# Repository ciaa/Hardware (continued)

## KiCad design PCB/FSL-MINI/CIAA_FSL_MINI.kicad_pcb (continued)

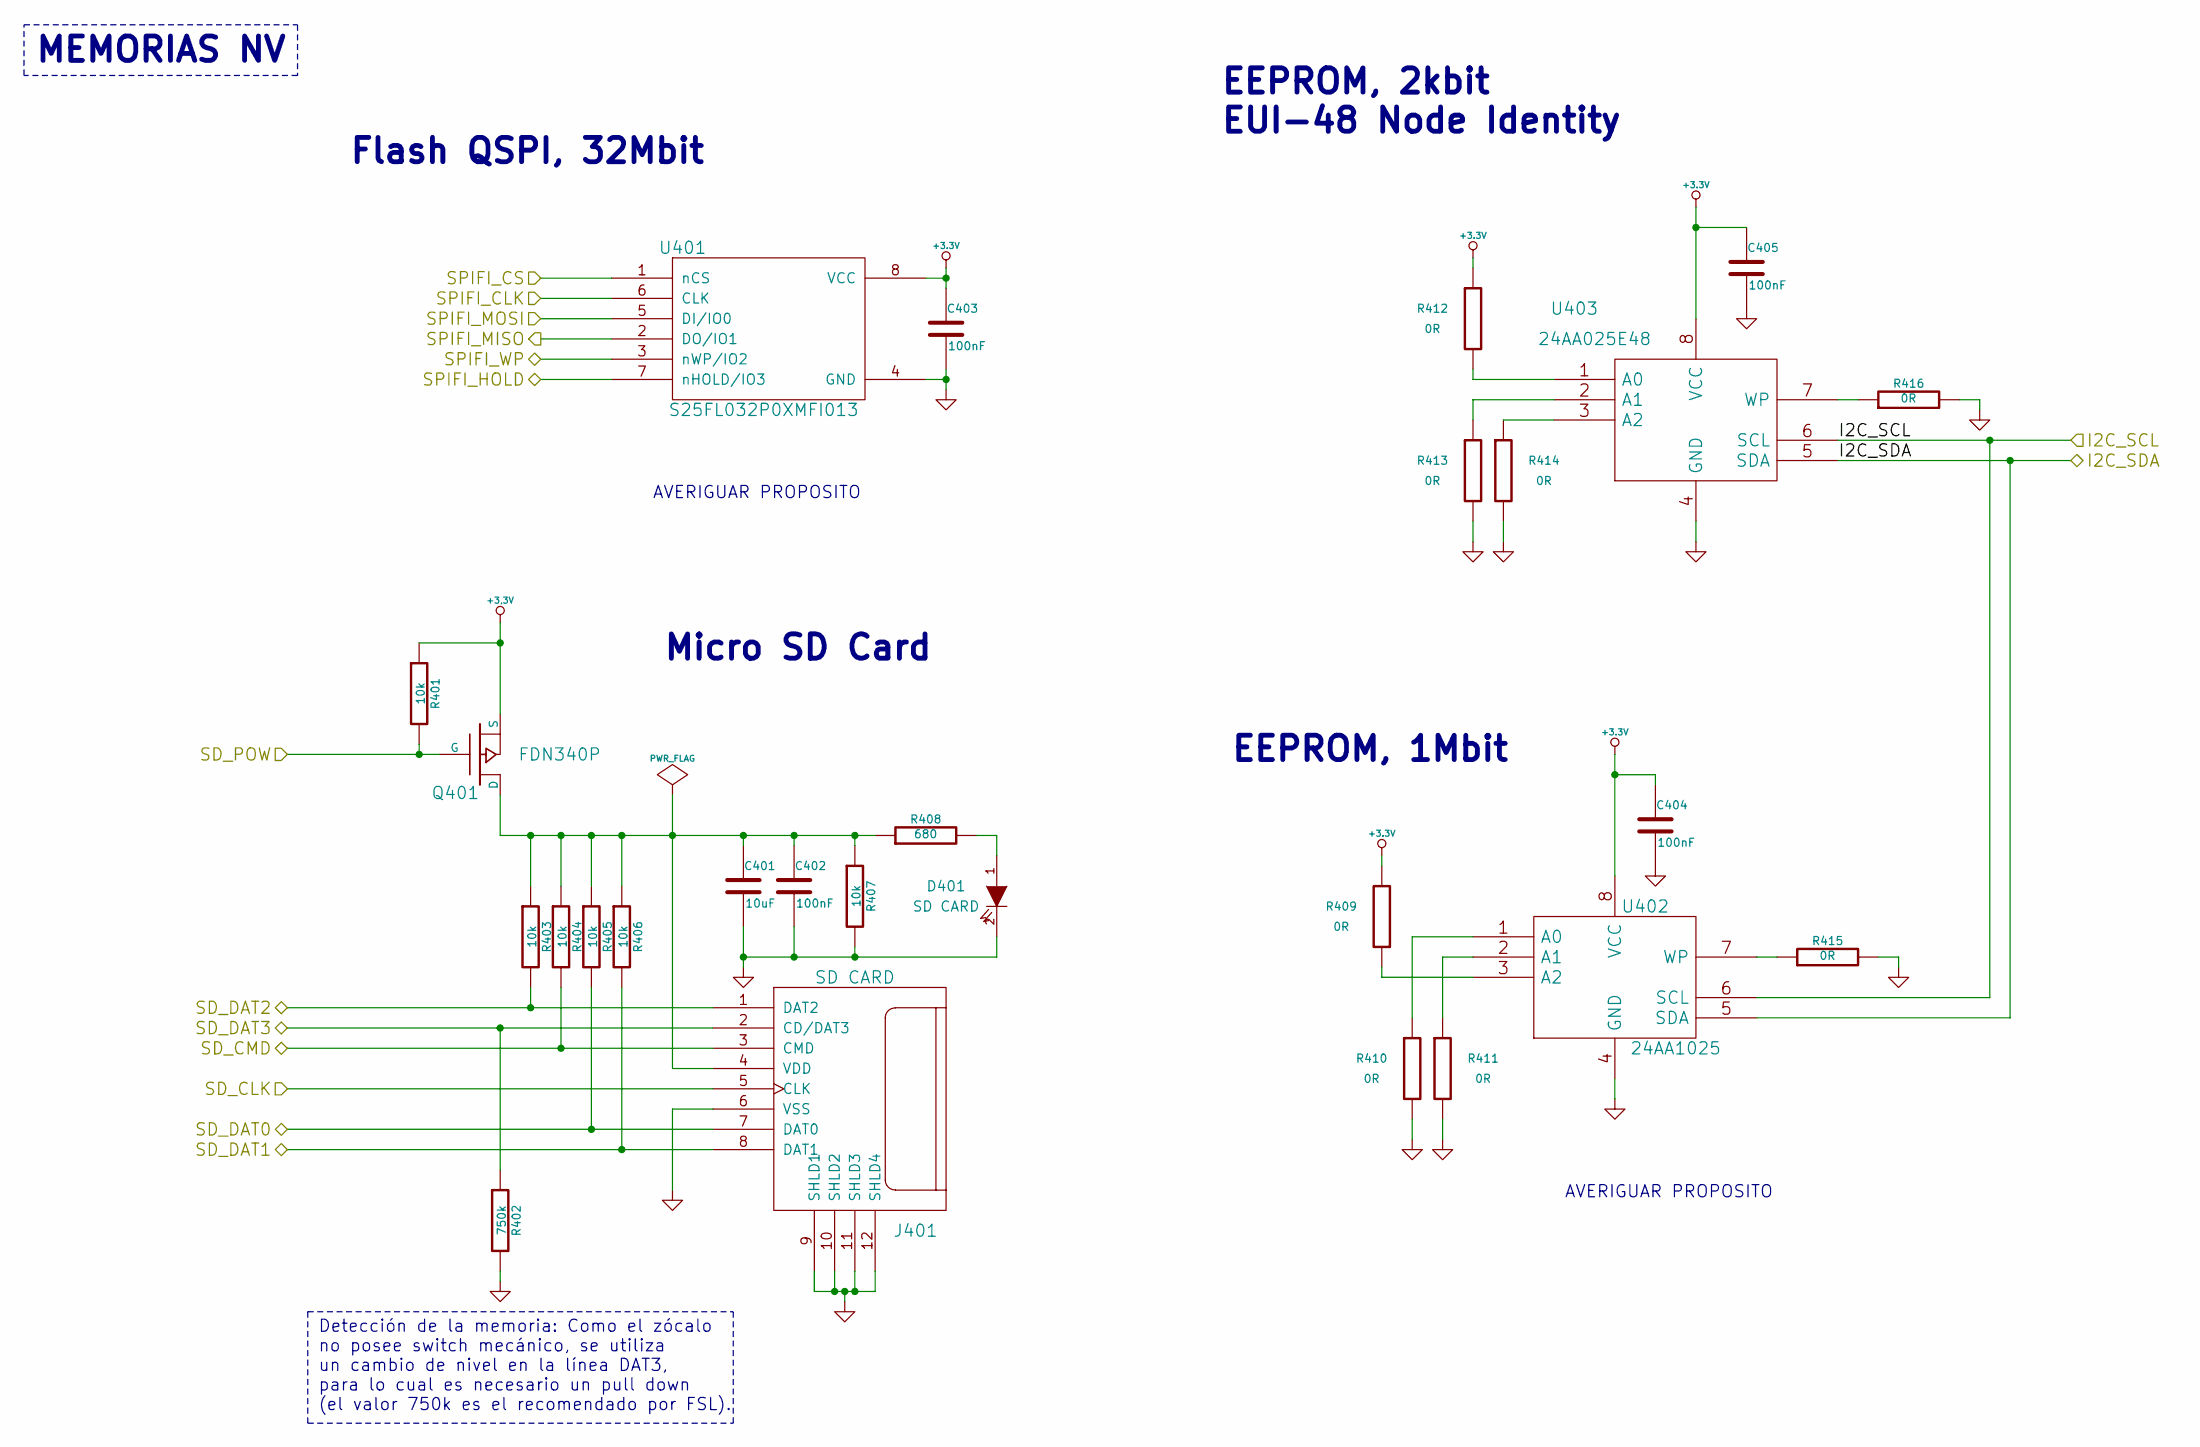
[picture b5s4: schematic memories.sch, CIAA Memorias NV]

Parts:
C401: 10uF; c_1206POL; Digikey/Mouser 399-10116-1-ND
C402, C403, C404, C405: 100nF; c_0603; Digikey/Mouser 399-1096-1-ND
D401: SD CARD; LED-0603; Digikey/Mouser 1080-1399-1-ND
J401: SD CARD; MicroSD_Hinged; Digikey/Mouser WM6698CT-ND
Q401: FDN340P; SOT-23; Digikey/Mouser FDN340PCT-ND
R401, R403, R404, R405, R406, R407: 10k; r_0603; Digikey/Mouser 311-10KGRCT-ND
R402: 750k; r_0603; Digikey/Mouser 311-750KGRCT-ND
R408: 680; r_0603; Digikey/Mouser 311-680GRCT-ND
R409, R410, R411, R412, R413, R414, R415, R416: 0R; r_0603; Digikey/Mouser 311-0.0GRCT-ND
U401: S25FL032P0XMFI013; SOIC-8_WIDE; Digikey/Mouser S25FL032P0XMFI013-ND
U402: 24AA1025; SOIC-8; Digikey/Mouser 24AA1025-I/SN-ND
U403: 24AA025E48; SOIC-8; Digikey/Mouser 24AA025E48-I/SN-ND

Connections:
/CPU/I2C_SCL: U402.6 (SCL), U403.6 (SCL); also elsewhere on the board
/CPU/I2C_SDA: U402.5 (SDA), U403.5 (SDA); also elsewhere on the board
/CPU/SD_CLK: J401.5 (CLK); also elsewhere on the board
/CPU/SD_CMD: J401.3 (CMD), R404.2; also elsewhere on the board
/CPU/SD_DAT0: J401.7 (DAT0), R405.2; also elsewhere on the board
/CPU/SD_DAT1: J401.8 (DAT1), R406.2; also elsewhere on the board
/CPU/SD_DAT2: J401.1 (DAT2), R403.2; also elsewhere on the board
/CPU/SD_DAT3: J401.2 (CD/DAT3), R402.1; also elsewhere on the board
/CPU/SD_POW: Q401.1 (G), R401.2; also elsewhere on the board
/CPU/SPIFI_CLK: U401.6 (CLK); also elsewhere on the board
/CPU/SPIFI_CS: U401.1 (nCS); also elsewhere on the board
/CPU/SPIFI_HOLD: U401.7 (nHOLD/IO3); also elsewhere on the board
/CPU/SPIFI_MISO: U401.2 (DO/IO1); also elsewhere on the board
/CPU/SPIFI_MOSI: U401.5 (DI/IO0); also elsewhere on the board
/CPU/SPIFI_WP: U401.3 (nWP/IO2); also elsewhere on the board
GND: C401.2, C402.2, C403.2, C404.2, C405.2, D401.2 (K), J401.6 (VSS), J401.9 (SHLD1), J401.10 (SHLD2), J401.11 (SHLD3), J401.12 (SHLD4), R402.2, R407.2, R410.2, R411.2, R413.2, R414.2, R415.2, R416.2, U401.4 (GND), U402.4 (GND), U403.4 (GND); also elsewhere on the board
unnamed: C401.1, C402.1, J401.4 (VDD), Q401.3 (D), R403.1, R404.1, R405.1, R406.1, R407.1, R408.1
unnamed: D401.1 (A), R408.2
unnamed: R409.1, U402.3 (A2)
unnamed: R410.1, U402.1 (A0)
unnamed: R411.1, U402.2 (A1)
unnamed: R412.2, U403.1 (A0)
unnamed: R413.1, U403.2 (A1)
unnamed: R414.1, U403.3 (A2)
unnamed: R415.1, U402.7 (WP)
unnamed: R416.1, U403.7 (WP)

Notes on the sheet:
EEPROM, 1Mbit
EEPROM, 2kbit EUI-48 Node Identity
Flash QSPI, 32Mbit
Micro SD Card
MEMORIAS NV
Detección de la memoria: Como el zócalo no posee switch mecánico, se utiliza un cambio de nivel en la línea DAT3, para lo cual es necesario un pull down (el valor 750k es el recomendado por FSL).
AVERIGUAR PROPOSITO

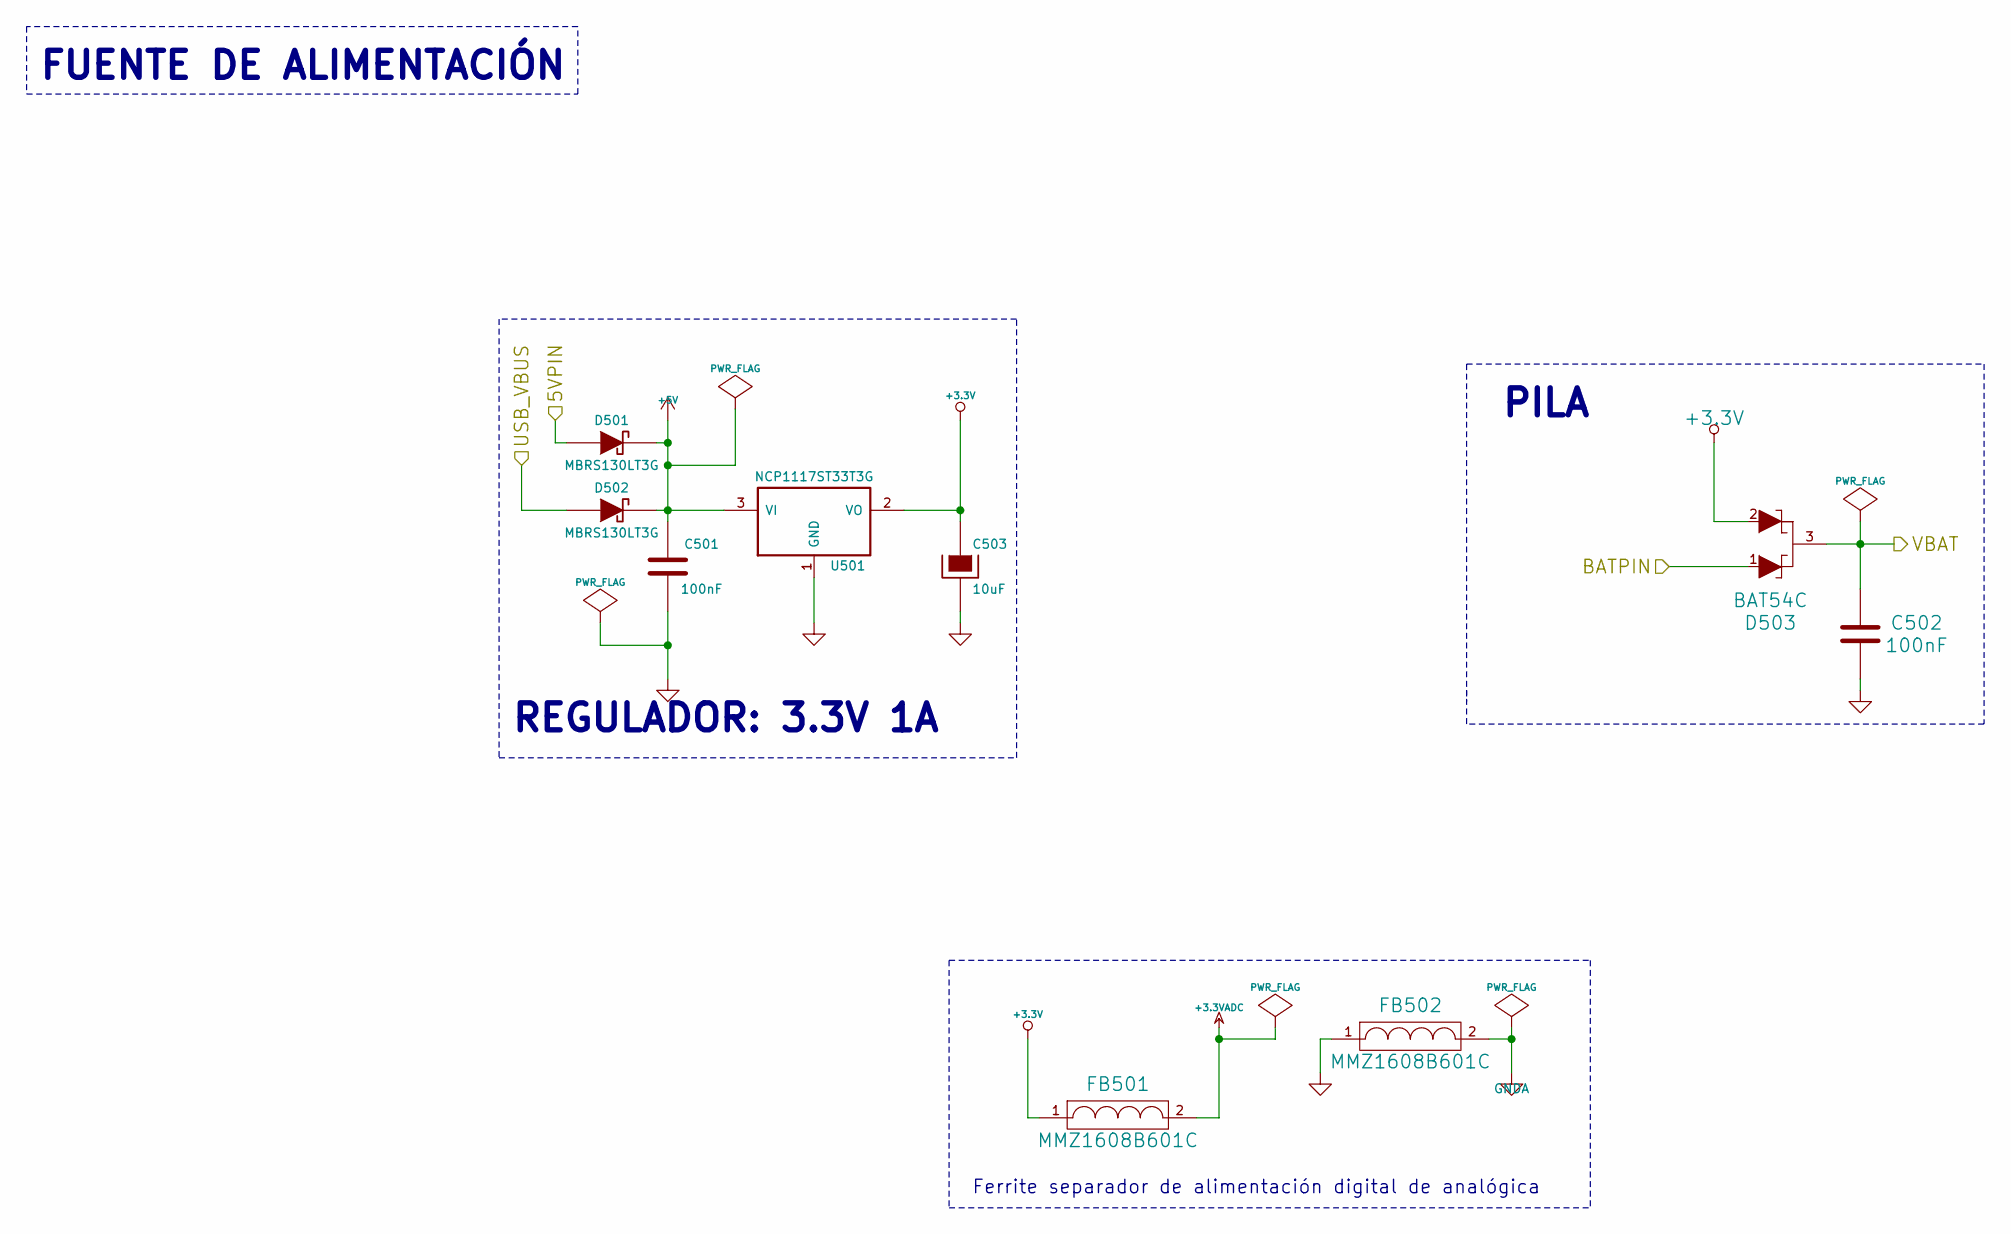
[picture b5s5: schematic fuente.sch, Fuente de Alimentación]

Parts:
C501, C502: 100nF; c_0603; Digikey/Mouser 399-1096-1-ND
C503: 10uF; c_1206POL; Digikey/Mouser 399-10116-1-ND
D501, D502: MBRS130LT3G; DO-214AA_SMB; Digikey/Mouser MBRS130LT3GOSCT-ND
D503: BAT54C; SOT-23; Digikey/Mouser BAT54FSCT-ND
FB501, FB502: MMZ1608B601C; fb_0603; Digikey/Mouser 445-2166-1-ND
U501: NCP1117ST33T3G; SOT-223; Digikey/Mouser NCP1117ST33T3GOSCT-ND

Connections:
+3.3VADC: FB501.2; also elsewhere on the board
+5V: C501.1, D501.2 (K), D502.2 (K), U501.3 (VI); also elsewhere on the board
/5VPIN: D501.1 (A); also elsewhere on the board
/BATPIN: D503.1 (B); also elsewhere on the board
/USB_VBUS: D502.1 (A); also elsewhere on the board
/VBAT: C502.1, D503.3 (C); also elsewhere on the board
GND: C501.2, C502.2, C503.2, FB502.1, U501.1 (GND); also elsewhere on the board
GNDA: FB502.2; also elsewhere on the board

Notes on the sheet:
Ferrite separador de alimentación digital de analógica
FUENTE DE ALIMENTACIÓN
REGULADOR: 3.3V 1A
PILA

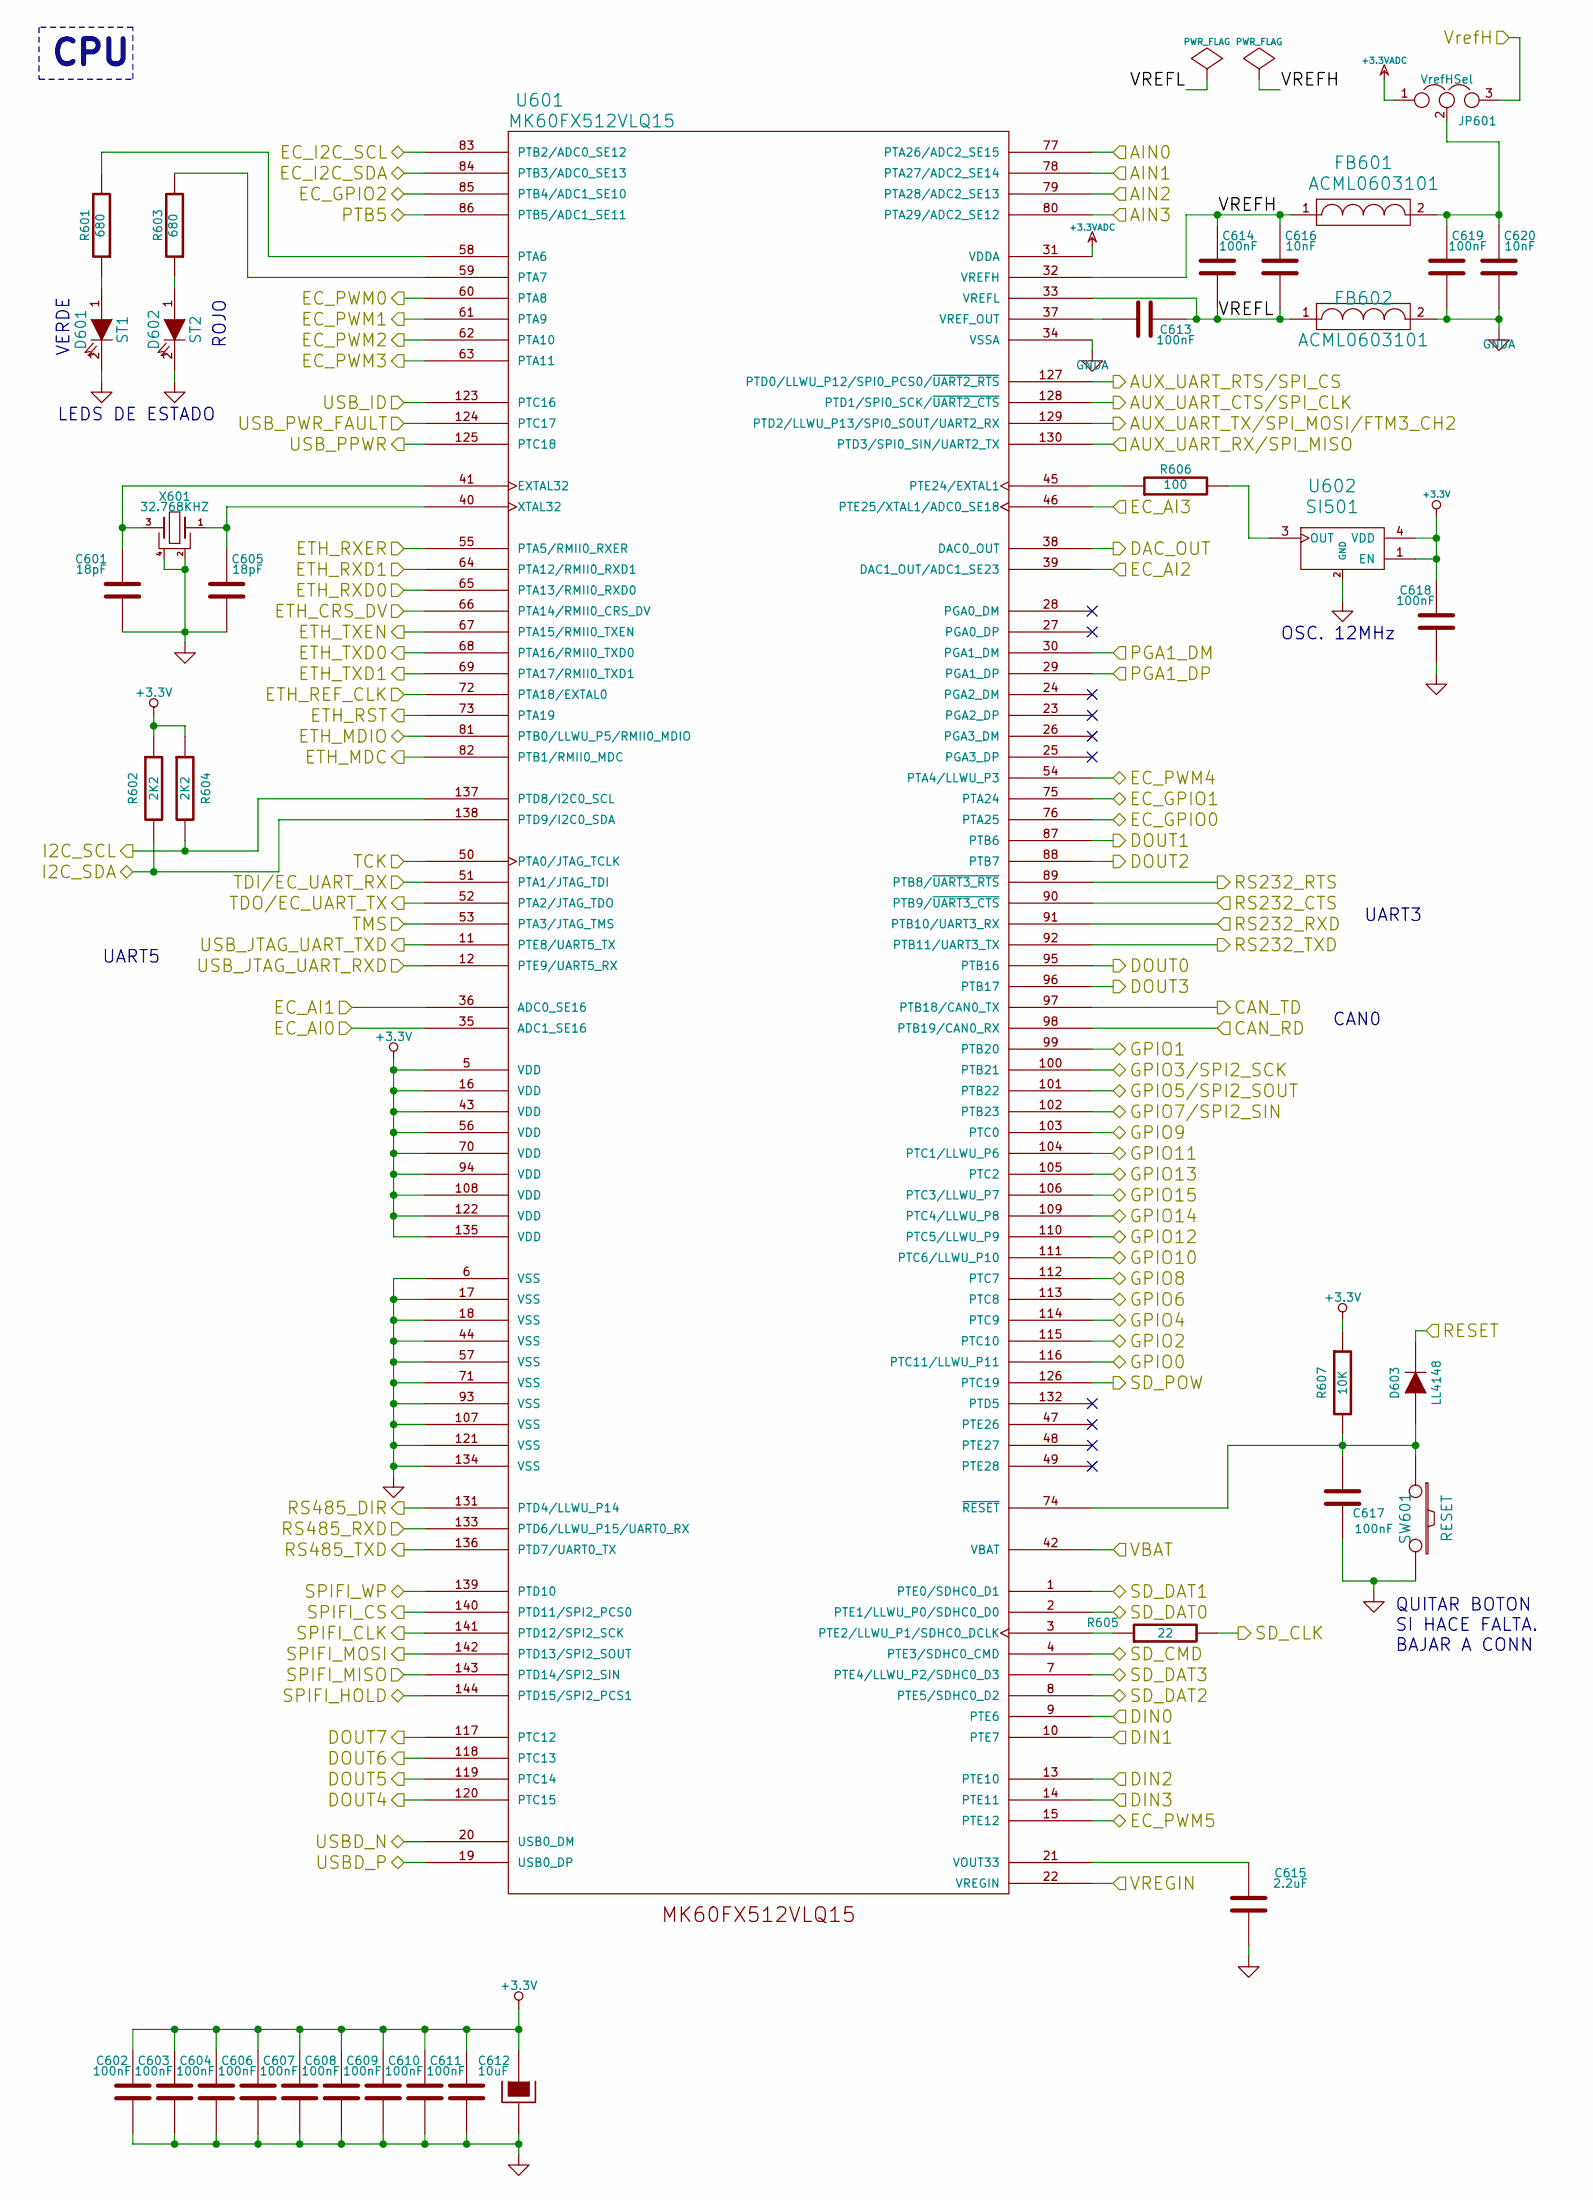
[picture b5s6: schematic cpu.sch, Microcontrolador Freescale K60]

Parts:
C601, C605: 18pF; c_0603; Digikey/Mouser 399-1052-1-ND
C602, C603, C604, C606, C607, C608, C609, C610, C611, C613, C614, C617, C618, C619: 100nF; c_0603; Digikey/Mouser 399-1096-1-ND
C612: 10uF; c_1206POL; Digikey/Mouser 399-10116-1-ND
C615: 2.2uF; c_0603; Digikey/Mouser 587-2983-1-ND
C616, C620: 10nF; c_0603; Digikey/Mouser 399-1091-1-ND
D601: ST1; LED-0603; Digikey/Mouser 1080-1399-1-ND
D602: ST2; LED-0603; Digikey/Mouser 1080-1400-1-ND
D603: LL4148; SOD-123; Digikey/Mouser LL4148FSCT-ND
FB601, FB602: ACML0603101; fb_0603; Digikey/Mouser ACML-0603-101-TCT-ND
JP601: VrefHSel; Pin_Header_Straight_1x03
R601, R603: 680; r_0603; Digikey/Mouser 311-680GRCT-ND
R602, R604: 2K2; r_0603; Digikey/Mouser 311-2.2KGRCT-ND
R605: 22; r_0603; Digikey/Mouser 311-22GRCT-ND
R606: 100; r_0603; Digikey/Mouser 311-100GRCT-ND
R607: 10K; r_0603; Digikey/Mouser 311-10KGRCT-ND
SW601: RESET; TACT_SMD_4; Digikey/Mouser 2-1437565-9
U601: MK60FX512VLQ15; LQFP144; Digikey/Mouser MK60FX512VLQ15-ND
U602: SI501; SI501_C; Digikey/Mouser 336-2889-ND
X601: 32.768KHZ; 4SOJ; Digikey/Mouser 535-9166-1-ND

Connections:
+3.3VADC: JP601.1, U601.31 (VDDA); also elsewhere on the board
/CPU/AIN0: U601.77 (PTA26/ADC2_SE15); also elsewhere on the board
/CPU/AIN1: U601.78 (PTA27/ADC2_SE14); also elsewhere on the board
/CPU/AIN2: U601.79 (PTA28/ADC2_SE13); also elsewhere on the board
/CPU/AIN3: U601.80 (PTA29/ADC2_SE12); also elsewhere on the board
/CPU/AUX_UART_CTS/SPI_CLK: U601.128 (PTD1/SPI0_SCK/~UART2_CTS); also elsewhere on the board
/CPU/AUX_UART_RTS/SPI_CS: U601.127 (PTD0/LLWU_P12/SPI0_PCS0/~UART2_RTS); also elsewhere on the board
/CPU/AUX_UART_RX/SPI_MISO: U601.130 (PTD3/SPI0_SIN/UART2_TX); also elsewhere on the board
/CPU/AUX_UART_TX/SPI_MOSI/FTM3_CH2: U601.129 (PTD2/LLWU_P13/SPI0_SOUT/UART2_RX); also elsewhere on the board
/CPU/CAN_RD: U601.98 (PTB19/CAN0_RX); also elsewhere on the board
/CPU/CAN_TD: U601.97 (PTB18/CAN0_TX); also elsewhere on the board
/CPU/DAC_OUT: U601.38 (DAC0_OUT); also elsewhere on the board
/CPU/DIN0: U601.9 (PTE6); also elsewhere on the board
/CPU/DIN1: U601.10 (PTE7); also elsewhere on the board
/CPU/DIN2: U601.13 (PTE10); also elsewhere on the board
/CPU/DIN3: U601.14 (PTE11); also elsewhere on the board
/CPU/DOUT0: U601.95 (PTB16); also elsewhere on the board
/CPU/DOUT1: U601.87 (PTB6); also elsewhere on the board
/CPU/DOUT2: U601.88 (PTB7); also elsewhere on the board
/CPU/DOUT3: U601.96 (PTB17); also elsewhere on the board
/CPU/DOUT4: U601.120 (PTC15); also elsewhere on the board
/CPU/DOUT5: U601.119 (PTC14); also elsewhere on the board
/CPU/DOUT6: U601.118 (PTC13); also elsewhere on the board
/CPU/DOUT7: U601.117 (PTC12); also elsewhere on the board
/CPU/EC_AI0: U601.35 (ADC1_SE16); also elsewhere on the board
/CPU/EC_AI1: U601.36 (ADC0_SE16); also elsewhere on the board
/CPU/EC_AI2: U601.39 (DAC1_OUT/ADC1_SE23); also elsewhere on the board
/CPU/EC_AI3: U601.46 (PTE25/XTAL1/ADC0_SE18); also elsewhere on the board
/CPU/EC_GPIO0: U601.76 (PTA25); also elsewhere on the board
/CPU/EC_GPIO1: U601.75 (PTA24); also elsewhere on the board
/CPU/EC_GPIO2: U601.85 (PTB4/ADC1_SE10); also elsewhere on the board
/CPU/EC_I2C_SCL: U601.83 (PTB2/ADC0_SE12); also elsewhere on the board
/CPU/EC_I2C_SDA: U601.84 (PTB3/ADC0_SE13); also elsewhere on the board
/CPU/EC_PWM0: U601.60 (PTA8); also elsewhere on the board
/CPU/EC_PWM1: U601.61 (PTA9); also elsewhere on the board
/CPU/EC_PWM2: U601.62 (PTA10); also elsewhere on the board
/CPU/EC_PWM3: U601.63 (PTA11); also elsewhere on the board
/CPU/EC_PWM4: U601.54 (PTA4/LLWU_P3); also elsewhere on the board
/CPU/EC_PWM5: U601.15 (PTE12); also elsewhere on the board
/CPU/ETH_CRS_DV: U601.66 (PTA14/RMII0_CRS_DV); also elsewhere on the board
/CPU/ETH_MDC: U601.82 (PTB1/RMII0_MDC); also elsewhere on the board
/CPU/ETH_MDIO: U601.81 (PTB0/LLWU_P5/RMII0_MDIO); also elsewhere on the board
/CPU/ETH_REF_CLK: U601.72 (PTA18/EXTAL0); also elsewhere on the board
/CPU/ETH_RST: U601.73 (PTA19); also elsewhere on the board
/CPU/ETH_RXD0: U601.65 (PTA13/RMII0_RXD0); also elsewhere on the board
/CPU/ETH_RXD1: U601.64 (PTA12/RMII0_RXD1); also elsewhere on the board
/CPU/ETH_RXER: U601.55 (PTA5/RMII0_RXER); also elsewhere on the board
/CPU/ETH_TXD0: U601.68 (PTA16/RMII0_TXD0); also elsewhere on the board
/CPU/ETH_TXD1: U601.69 (PTA17/RMII0_TXD1); also elsewhere on the board
/CPU/ETH_TXEN: U601.67 (PTA15/RMII0_TXEN); also elsewhere on the board
/CPU/GPIO0: U601.116 (PTC11/LLWU_P11); also elsewhere on the board
/CPU/GPIO1: U601.99 (PTB20); also elsewhere on the board
/CPU/GPIO2: U601.115 (PTC10); also elsewhere on the board
/CPU/GPIO3/SPI2_SCK: U601.100 (PTB21); also elsewhere on the board
/CPU/GPIO4: U601.114 (PTC9); also elsewhere on the board
/CPU/GPIO5/SPI2_SOUT: U601.101 (PTB22); also elsewhere on the board
/CPU/GPIO6: U601.113 (PTC8); also elsewhere on the board
/CPU/GPIO7/SPI2_SIN: U601.102 (PTB23); also elsewhere on the board
/CPU/GPIO8: U601.112 (PTC7); also elsewhere on the board
/CPU/GPIO9: U601.103 (PTC0); also elsewhere on the board
/CPU/GPIO10: U601.111 (PTC6/LLWU_P10); also elsewhere on the board
/CPU/GPIO11: U601.104 (PTC1/LLWU_P6); also elsewhere on the board
/CPU/GPIO12: U601.110 (PTC5/LLWU_P9); also elsewhere on the board
/CPU/GPIO13: U601.105 (PTC2); also elsewhere on the board
/CPU/GPIO14: U601.109 (PTC4/LLWU_P8); also elsewhere on the board
/CPU/GPIO15: U601.106 (PTC3/LLWU_P7); also elsewhere on the board
/CPU/I2C_SCL: R604.2, U601.137 (PTD8/I2C0_SCL); also elsewhere on the board
/CPU/I2C_SDA: R602.2, U601.138 (PTD9/I2C0_SDA); also elsewhere on the board
/CPU/PGA1_DM: U601.30 (PGA1_DM); also elsewhere on the board
/CPU/PGA1_DP: U601.29 (PGA1_DP); also elsewhere on the board
/CPU/PTB5: U601.86 (PTB5/ADC1_SE11); also elsewhere on the board
/CPU/RS232_CTS: U601.90 (PTB9/~UART3_CTS); also elsewhere on the board
/CPU/RS232_RTS: U601.89 (PTB8/~UART3_RTS); also elsewhere on the board
/CPU/RS232_RXD: U601.91 (PTB10/UART3_RX); also elsewhere on the board
/CPU/RS232_TXD: U601.92 (PTB11/UART3_TX); also elsewhere on the board
/CPU/RS485_DIR: U601.131 (PTD4/LLWU_P14); also elsewhere on the board
/CPU/RS485_RXD: U601.133 (PTD6/LLWU_P15/UART0_RX); also elsewhere on the board
/CPU/RS485_TXD: U601.136 (PTD7/UART0_TX); also elsewhere on the board
/CPU/SD_CLK: R605.2; also elsewhere on the board
/CPU/SD_CMD: U601.4 (PTE3/SDHC0_CMD); also elsewhere on the board
/CPU/SD_DAT0: U601.2 (PTE1/LLWU_P0/SDHC0_D0); also elsewhere on the board
/CPU/SD_DAT1: U601.1 (PTE0/SDHC0_D1); also elsewhere on the board
/CPU/SD_DAT2: U601.8 (PTE5/SDHC0_D2); also elsewhere on the board
/CPU/SD_DAT3: U601.7 (PTE4/LLWU_P2/SDHC0_D3); also elsewhere on the board
/CPU/SD_POW: U601.126 (PTC19); also elsewhere on the board
/CPU/SPIFI_CLK: U601.141 (PTD12/SPI2_SCK); also elsewhere on the board
/CPU/SPIFI_CS: U601.140 (PTD11/SPI2_PCS0); also elsewhere on the board
/CPU/SPIFI_HOLD: U601.144 (PTD15/SPI2_PCS1); also elsewhere on the board
/CPU/SPIFI_MISO: U601.143 (PTD14/SPI2_SIN); also elsewhere on the board
/CPU/SPIFI_MOSI: U601.142 (PTD13/SPI2_SOUT); also elsewhere on the board
/CPU/SPIFI_WP: U601.139 (PTD10); also elsewhere on the board
/CPU/USBD_N: U601.20 (USB0_DM); also elsewhere on the board
/CPU/USBD_P: U601.19 (USB0_DP); also elsewhere on the board
/CPU/USB_ID: U601.123 (PTC16); also elsewhere on the board
/CPU/VREFL: C613.2, C614.2, C616.1, FB602.1, U601.33 (VREFL)
/I/O/ArefA: C614.1, C616.2, FB601.1, JP601.3, U601.32 (VREFH); also elsewhere on the board
/RESET: D603.2 (K); also elsewhere on the board
/TCK: U601.50 (PTA0/JTAG_TCLK); also elsewhere on the board
/TDI/EC_UART_RX: U601.51 (PTA1/JTAG_TDI); also elsewhere on the board
/TDO/EC_UART_TX: U601.52 (PTA2/JTAG_TDO); also elsewhere on the board
/TMS: U601.53 (PTA3/JTAG_TMS); also elsewhere on the board
/USB OTG/USB0_PPWR: U601.125 (PTC18); also elsewhere on the board
/USB OTG/USB0_PWR_FAULT: U601.124 (PTC17); also elsewhere on the board
/USB_JTAG_UART_RXD: U601.12 (PTE9/UART5_RX); also elsewhere on the board
/USB_JTAG_UART_TXD: U601.11 (PTE8/UART5_TX); also elsewhere on the board
/USB_VBUS: U601.22 (VREGIN); also elsewhere on the board
/VBAT: U601.42 (VBAT); also elsewhere on the board
GND: C601.2, C602.2, C603.2, C604.2, C605.2, C606.2, C607.2, C608.2, C609.2, C610.2, C611.2, C612.2, C615.2, C617.1, C618.2, D601.2 (K), D602.2 (K), SW601.2, U601.6 (VSS), U601.17 (VSS), U601.18 (VSS), U601.44 (VSS), U601.57 (VSS), U601.71 (VSS), U601.93 (VSS), U601.107 (VSS), U601.121 (VSS), U601.134 (VSS), U602.2 (GND), X601.2 (GND), X601.4 (GND); also elsewhere on the board
GNDA: C619.2, C620.1, FB602.2, U601.34 (VSSA); also elsewhere on the board
unnamed: C601.1, U601.41 (EXTAL32), X601.3 (B)
unnamed: C605.1, U601.40 (XTAL32), X601.1 (A)
unnamed: C613.1, U601.37 (VREF_OUT)
unnamed: C615.1, U601.21 (VOUT33)
unnamed: C617.2, D603.1 (A), R607.2, SW601.1, U601.74 (~RESET)
unnamed: C619.1, C620.2, FB601.2, JP601.2
unnamed: D601.1 (A), R601.1
unnamed: D602.1 (A), R603.1
unnamed: R601.2, U601.58 (PTA6)
unnamed: R603.2, U601.59 (PTA7)
unnamed: R605.1, U601.3 (PTE2/LLWU_P1/SDHC0_DCLK)
unnamed: R606.1, U601.45 (PTE24/EXTAL1)
unnamed: R606.2, U602.3 (OUT)

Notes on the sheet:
CPU
VERDE
ROJO
LEDS DE ESTADO
CAN0
UART3
UART5
OSC. 12MHz
QUITAR BOTON SI HACE FALTA. BAJAR A CONN

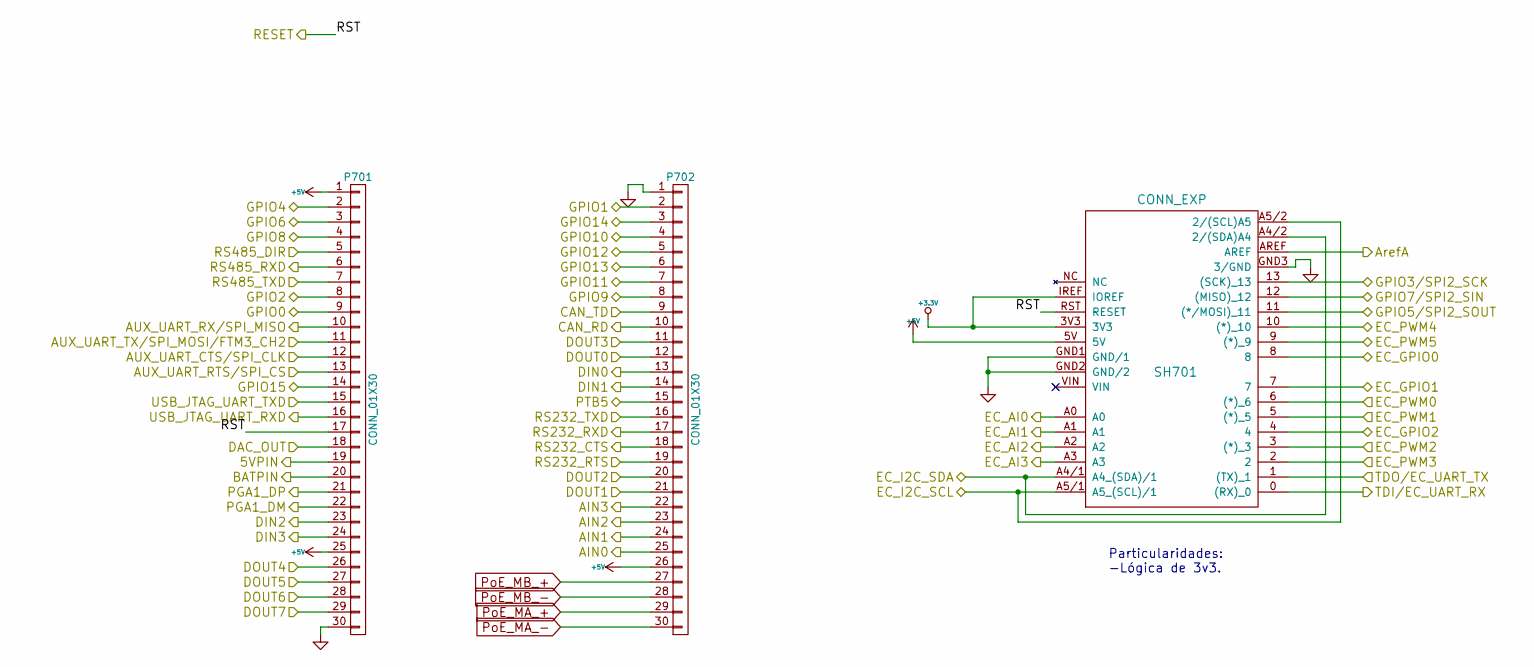
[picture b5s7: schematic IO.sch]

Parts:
P701, P702: CONN_01X30; Pin_Header_Straight_1x30
SH701: CONN_EXP; ARDUINO_as_UNO_R3

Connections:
+5V: P701.1, P701.25, P702.26, SH701.5V; also elsewhere on the board
/5VPIN: P701.19; also elsewhere on the board
/BATPIN: P701.20; also elsewhere on the board
/CPU/AIN0: P702.25; also elsewhere on the board
/CPU/AIN1: P702.24; also elsewhere on the board
/CPU/AIN2: P702.23; also elsewhere on the board
/CPU/AIN3: P702.22; also elsewhere on the board
/CPU/AUX_UART_CTS/SPI_CLK: P701.12; also elsewhere on the board
/CPU/AUX_UART_RTS/SPI_CS: P701.13; also elsewhere on the board
/CPU/AUX_UART_RX/SPI_MISO: P701.10; also elsewhere on the board
/CPU/AUX_UART_TX/SPI_MOSI/FTM3_CH2: P701.11; also elsewhere on the board
/CPU/CAN_RD: P702.10; also elsewhere on the board
/CPU/CAN_TD: P702.9; also elsewhere on the board
/CPU/DAC_OUT: P701.18; also elsewhere on the board
/CPU/DIN0: P702.13; also elsewhere on the board
/CPU/DIN1: P702.14; also elsewhere on the board
/CPU/DIN2: P701.23; also elsewhere on the board
/CPU/DIN3: P701.24; also elsewhere on the board
/CPU/DOUT0: P702.12; also elsewhere on the board
/CPU/DOUT1: P702.21; also elsewhere on the board
/CPU/DOUT2: P702.20; also elsewhere on the board
/CPU/DOUT3: P702.11; also elsewhere on the board
/CPU/DOUT4: P701.26; also elsewhere on the board
/CPU/DOUT5: P701.27; also elsewhere on the board
/CPU/DOUT6: P701.28; also elsewhere on the board
/CPU/DOUT7: P701.29; also elsewhere on the board
/CPU/EC_AI0: SH701.A0; also elsewhere on the board
/CPU/EC_AI1: SH701.A1; also elsewhere on the board
/CPU/EC_AI2: SH701.A2; also elsewhere on the board
/CPU/EC_AI3: SH701.A3; also elsewhere on the board
/CPU/EC_GPIO0: SH701.8; also elsewhere on the board
/CPU/EC_GPIO1: SH701.7; also elsewhere on the board
/CPU/EC_GPIO2: SH701.4; also elsewhere on the board
/CPU/EC_I2C_SCL: SH701.A5/1 (A5_(SCL)/1), SH701.A5/2 (2/(SCL)A5); also elsewhere on the board
/CPU/EC_I2C_SDA: SH701.A4/1 (A4_(SDA)/1), SH701.A4/2 (2/(SDA)A4); also elsewhere on the board
/CPU/EC_PWM0: SH701.6 ((*)_6); also elsewhere on the board
/CPU/EC_PWM1: SH701.5 ((*)_5); also elsewhere on the board
/CPU/EC_PWM2: SH701.3 ((*)_3); also elsewhere on the board
/CPU/EC_PWM3: SH701.2; also elsewhere on the board
/CPU/EC_PWM4: SH701.10 ((*)_10); also elsewhere on the board
/CPU/EC_PWM5: SH701.9 ((*)_9); also elsewhere on the board
/CPU/GPIO0: P701.9; also elsewhere on the board
/CPU/GPIO1: P702.2; also elsewhere on the board
/CPU/GPIO2: P701.8; also elsewhere on the board
/CPU/GPIO3/SPI2_SCK: SH701.13 ((SCK)_13); also elsewhere on the board
/CPU/GPIO4: P701.2; also elsewhere on the board
/CPU/GPIO5/SPI2_SOUT: SH701.11 ((*/MOSI)_11); also elsewhere on the board
/CPU/GPIO6: P701.3; also elsewhere on the board
/CPU/GPIO7/SPI2_SIN: SH701.12 ((MISO)_12); also elsewhere on the board
/CPU/GPIO8: P701.4; also elsewhere on the board
/CPU/GPIO9: P702.8; also elsewhere on the board
/CPU/GPIO10: P702.4; also elsewhere on the board
/CPU/GPIO11: P702.7; also elsewhere on the board
/CPU/GPIO12: P702.5; also elsewhere on the board
/CPU/GPIO13: P702.6; also elsewhere on the board
/CPU/GPIO14: P702.3; also elsewhere on the board
/CPU/GPIO15: P701.14; also elsewhere on the board
/CPU/PGA1_DM: P701.22; also elsewhere on the board
/CPU/PGA1_DP: P701.21; also elsewhere on the board
/CPU/PTB5: P702.15; also elsewhere on the board
/CPU/RS232_CTS: P702.18; also elsewhere on the board
/CPU/RS232_RTS: P702.19; also elsewhere on the board
/CPU/RS232_RXD: P702.17; also elsewhere on the board
/CPU/RS232_TXD: P702.16; also elsewhere on the board
/CPU/RS485_DIR: P701.5; also elsewhere on the board
/CPU/RS485_RXD: P701.6; also elsewhere on the board
/CPU/RS485_TXD: P701.7; also elsewhere on the board
/I/O/ArefA: SH701.AREF; also elsewhere on the board
/RESET: P701.17, SH701.RST (RESET); also elsewhere on the board
/TDI/EC_UART_RX: SH701.0 ((RX)_0); also elsewhere on the board
/TDO/EC_UART_TX: SH701.1 ((TX)_1); also elsewhere on the board
/USB_JTAG_UART_RXD: P701.16; also elsewhere on the board
/USB_JTAG_UART_TXD: P701.15; also elsewhere on the board
GND: P701.30, P702.1, SH701.GND1 (GND/1), SH701.GND2 (GND/2), SH701.GND3 (3/GND); also elsewhere on the board
PoE_MA_+: P702.29; also elsewhere on the board
PoE_MA_-: P702.30; also elsewhere on the board
PoE_MB_+: P702.27; also elsewhere on the board
PoE_MB_-: P702.28; also elsewhere on the board

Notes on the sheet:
Particularidades: -Lógica de 3v3.

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
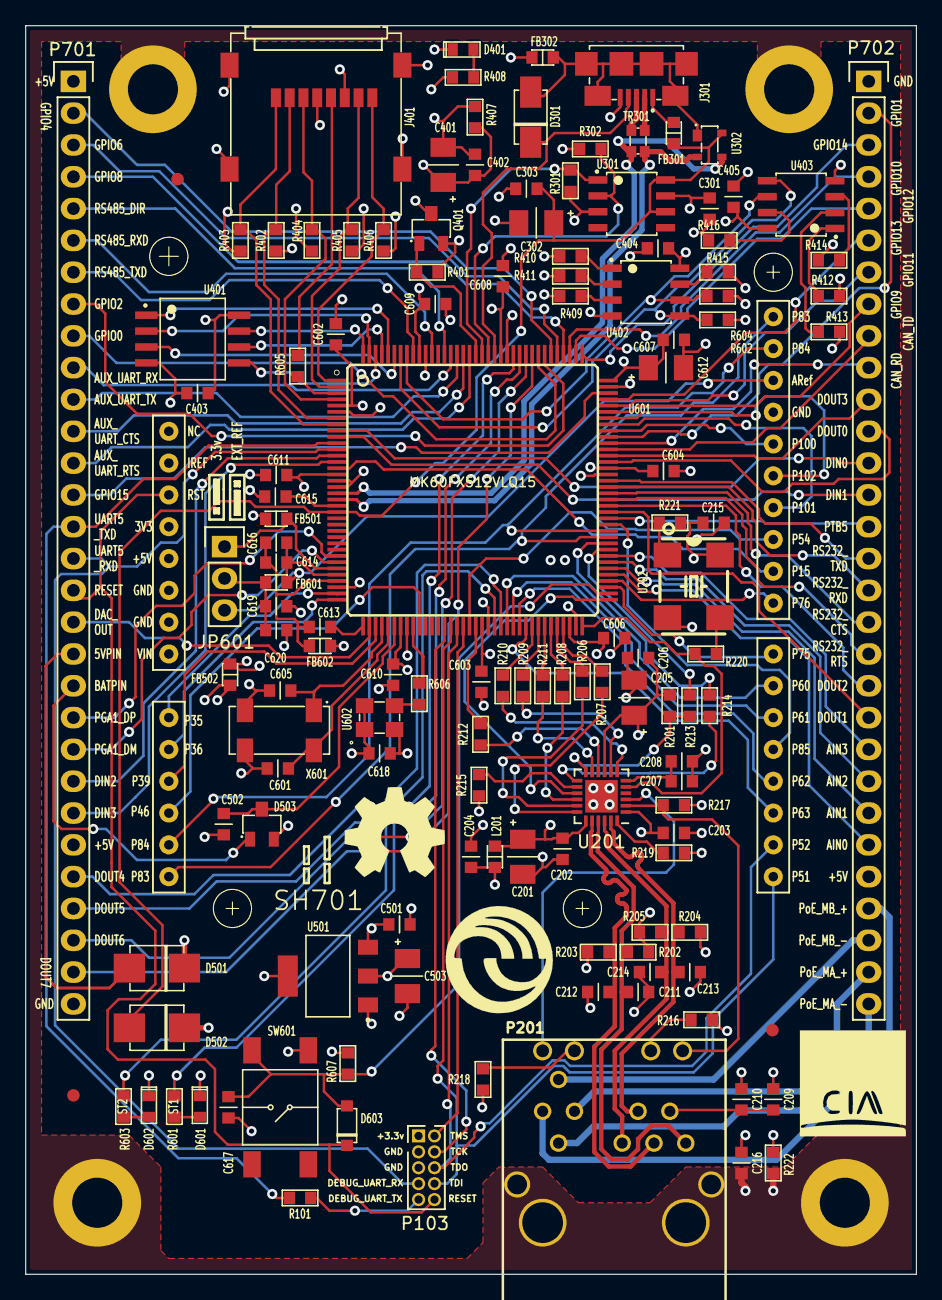
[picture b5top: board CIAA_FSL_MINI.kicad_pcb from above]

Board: 4 copper layers, 71.1 x 99.7 mm, 141 parts (0 on the bottom side), 169 nets.

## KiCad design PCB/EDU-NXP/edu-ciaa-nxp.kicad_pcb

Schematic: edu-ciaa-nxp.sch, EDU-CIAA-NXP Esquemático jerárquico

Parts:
F1, F2, F3, F4, F5, F6: fiducial
H1, H2, H3, H4: 4mm
TP1: 4mm; Digikey 36-5125-ND

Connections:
GND: TP1.1; also elsewhere on the board

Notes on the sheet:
Índice: 1. Esquemático jerárquico 2. RS485 3. USB OTG 4. GPIO 5. Fuente de alimentación 6. On Board IO 7. CPU
Fiduciales TOP BOTTOM
Holes
Computadora Industrial Abierta Argentina Versión Educativa EDU-CIAA (Procesador NXP)
PROYECTO CIAA http://www.proyecto-ciaa.com.ar/
GND pin
